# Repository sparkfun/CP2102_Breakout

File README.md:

CP2102 USB to Serial Breakout Board
===================================

[
*CP2102 USB to Serial Breakout (BOB-00198)*](https://www.sparkfun.com/products/198)

This breakout board enables you to connect to a standard USB A to B cable and communicate to your microcontroller via serial logic.

Repository Contents
-------------------
* **/Hardware** - All Eagle design files (.brd, .sch)
* **/Production** - Test bed files and production panel files

License Information
-------------------
The hardware is released under [Creative Commons ShareAlike 4.0 International](https://creativecommons.org/licenses/by-sa/4.0/).

Distributed as-is; no warranty is given.

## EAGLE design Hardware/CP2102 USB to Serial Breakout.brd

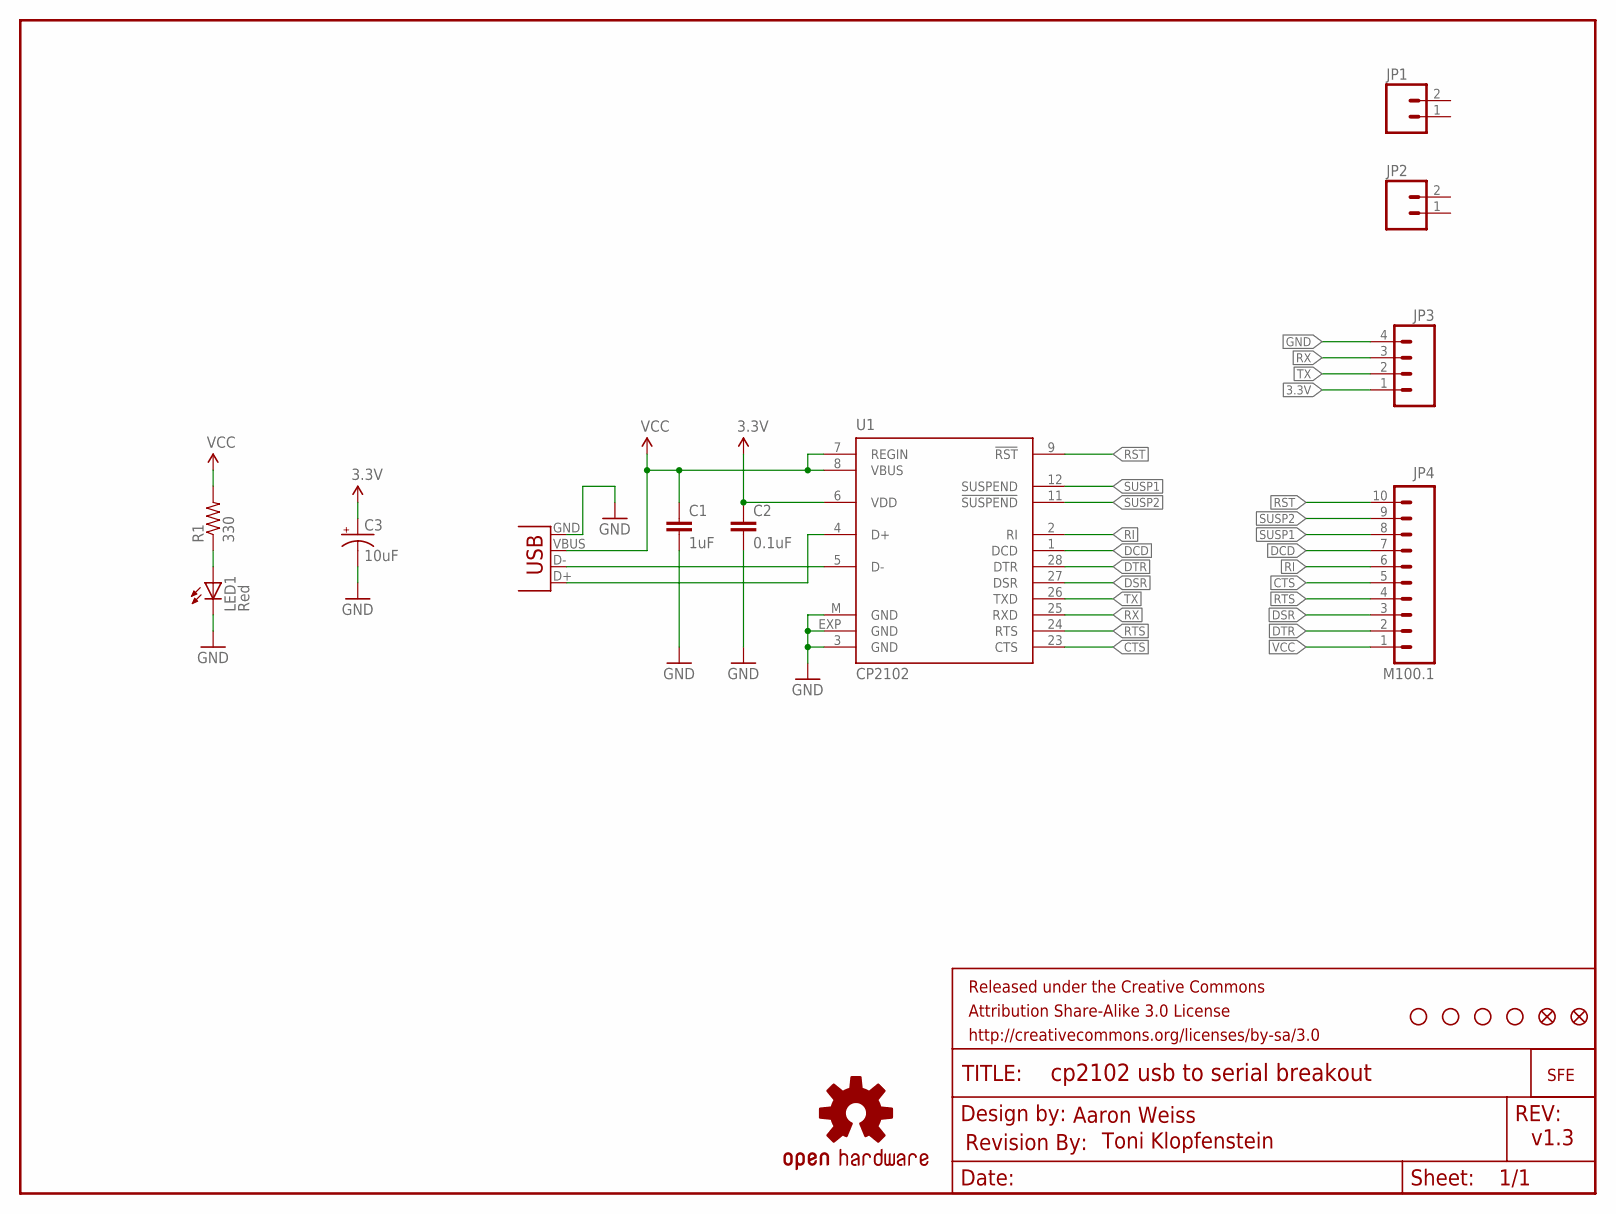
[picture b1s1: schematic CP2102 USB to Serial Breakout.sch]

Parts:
C1: 1uF; 0603-CAP
C2: 0.1uF; 0603-CAP
C3: 10uF; EIA3216
FID1, FID2: FIDUCIAL1X2; FIDUCIAL-1X2
FRAME1: FRAME-LETTER; CREATIVE_COMMONS
JP1, JP2: M02PTH; 1X02
JP3: M04PTH; 1X04
JP4: M100.1; 1X10
LED1: Red; LED-1206
LOGO1: OSHW-LOGOS; OSHW-LOGO-S
R1: 330; 0603-RES
U1: CP2102; MLP28
U$1: LOGO-SFENEW; SFE-NEW-WEBLOGO
U$4: REVISION
U$6, U$7, U$8, U$9: STAND-OFF
X1: USBPTH; USB-B-PTH

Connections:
3.3V: C2.1, C3.A (+), JP3.1, U1.6 (VDD)
CTS: JP4.5, U1.23 (CTS)
DCD: JP4.7, U1.1 (DCD)
DSR: JP4.3, U1.27 (DSR)
DTR: JP4.2, U1.28 (DTR)
GND: C1.2, C2.2, C3.C (-), JP3.4, LED1.C, U1.3 (GND), U1.EXP (GND), U1.M (GND), X1.GND
unnamed: U1.5 (D-), X1.D-
unnamed: U1.4 (D+), X1.D+
unnamed: LED1.A, R1.1
RI: JP4.6, U1.2 (RI)
RST: JP4.10, U1.9 (!RST)
RTS: JP4.4, U1.24 (RTS)
RX: JP3.3, U1.25 (RXD)
SUSP1: JP4.8, U1.12 (SUSPEND)
SUSP2: JP4.9, U1.11 (!SUSPEND)
TX: JP3.2, U1.26 (TXD)
VCC: C1.1, JP4.1, R1.2, U1.7 (REGIN), U1.8 (VBUS), X1.VBUS

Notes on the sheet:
Aaron Weiss
Toni Klopfenstein
v1.3

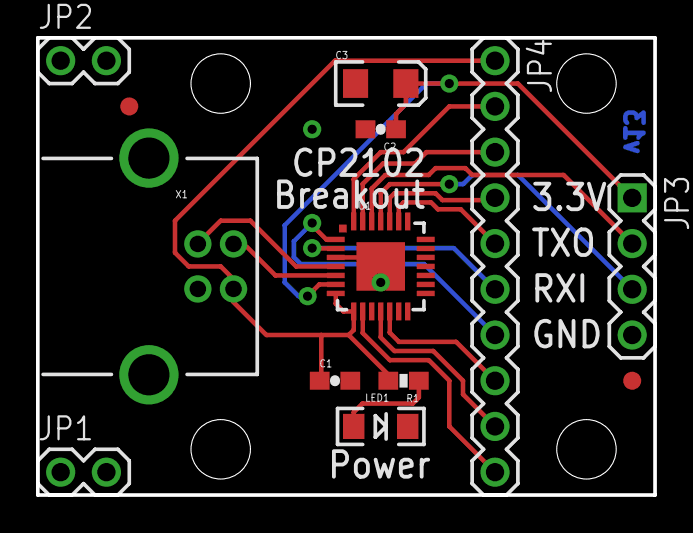
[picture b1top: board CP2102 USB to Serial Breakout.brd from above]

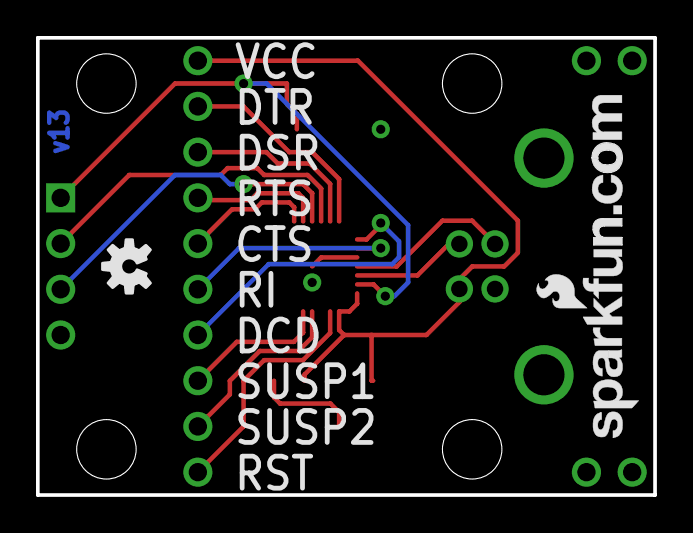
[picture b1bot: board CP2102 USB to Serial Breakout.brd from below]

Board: 2 copper layers, 34.3 x 25.4 mm, 21 parts (2 on the bottom side), 17 nets.

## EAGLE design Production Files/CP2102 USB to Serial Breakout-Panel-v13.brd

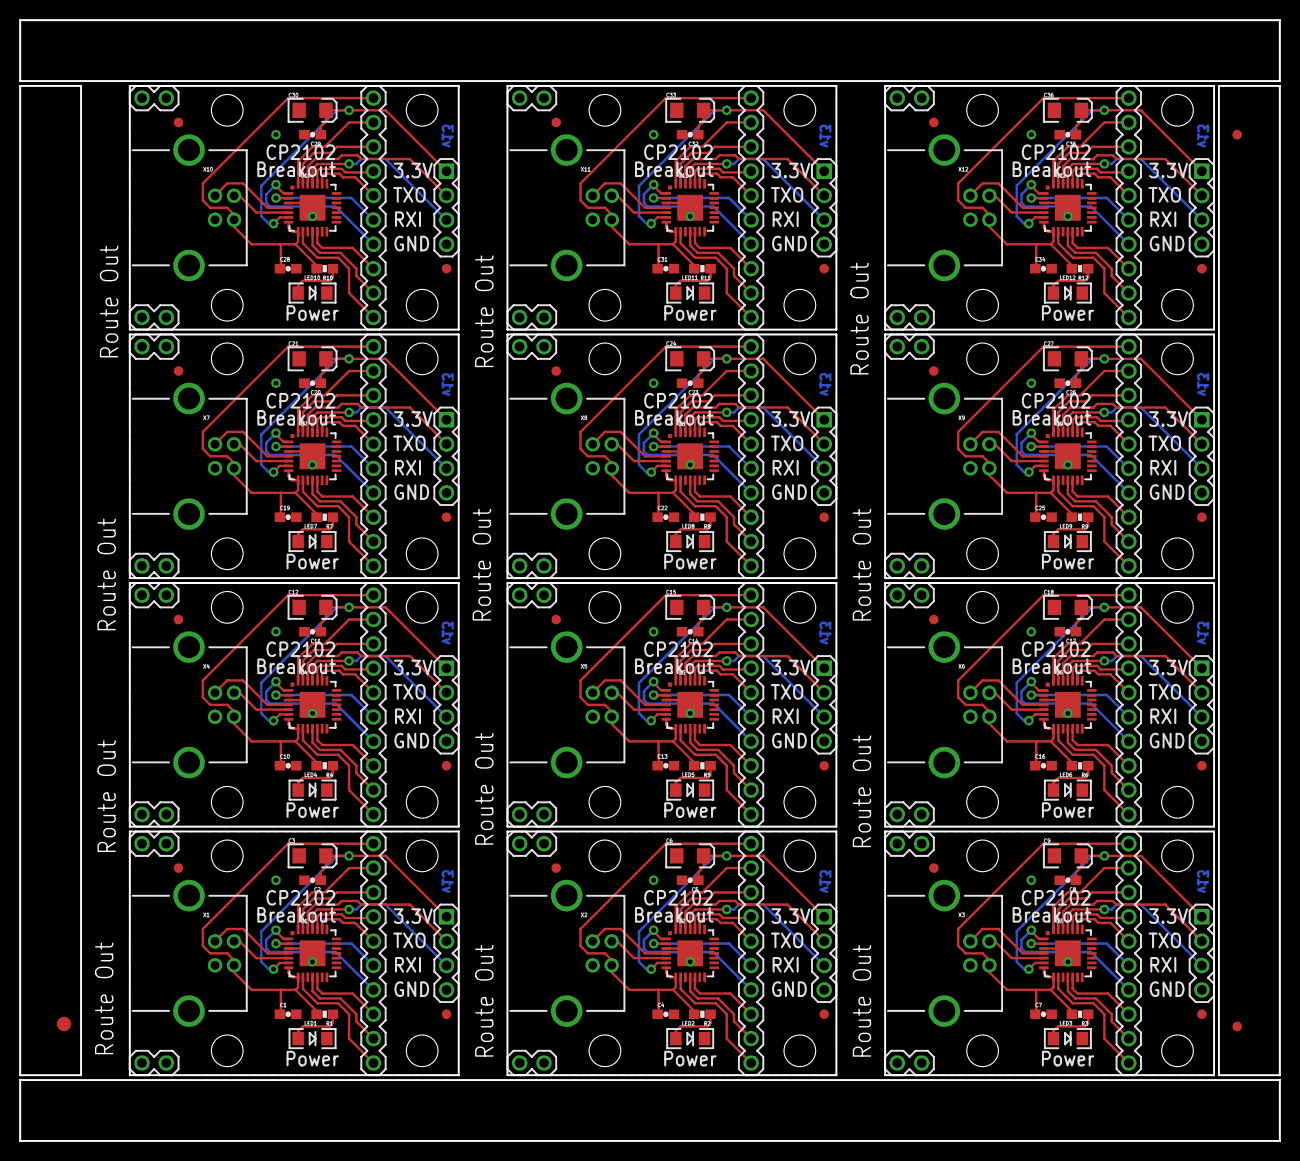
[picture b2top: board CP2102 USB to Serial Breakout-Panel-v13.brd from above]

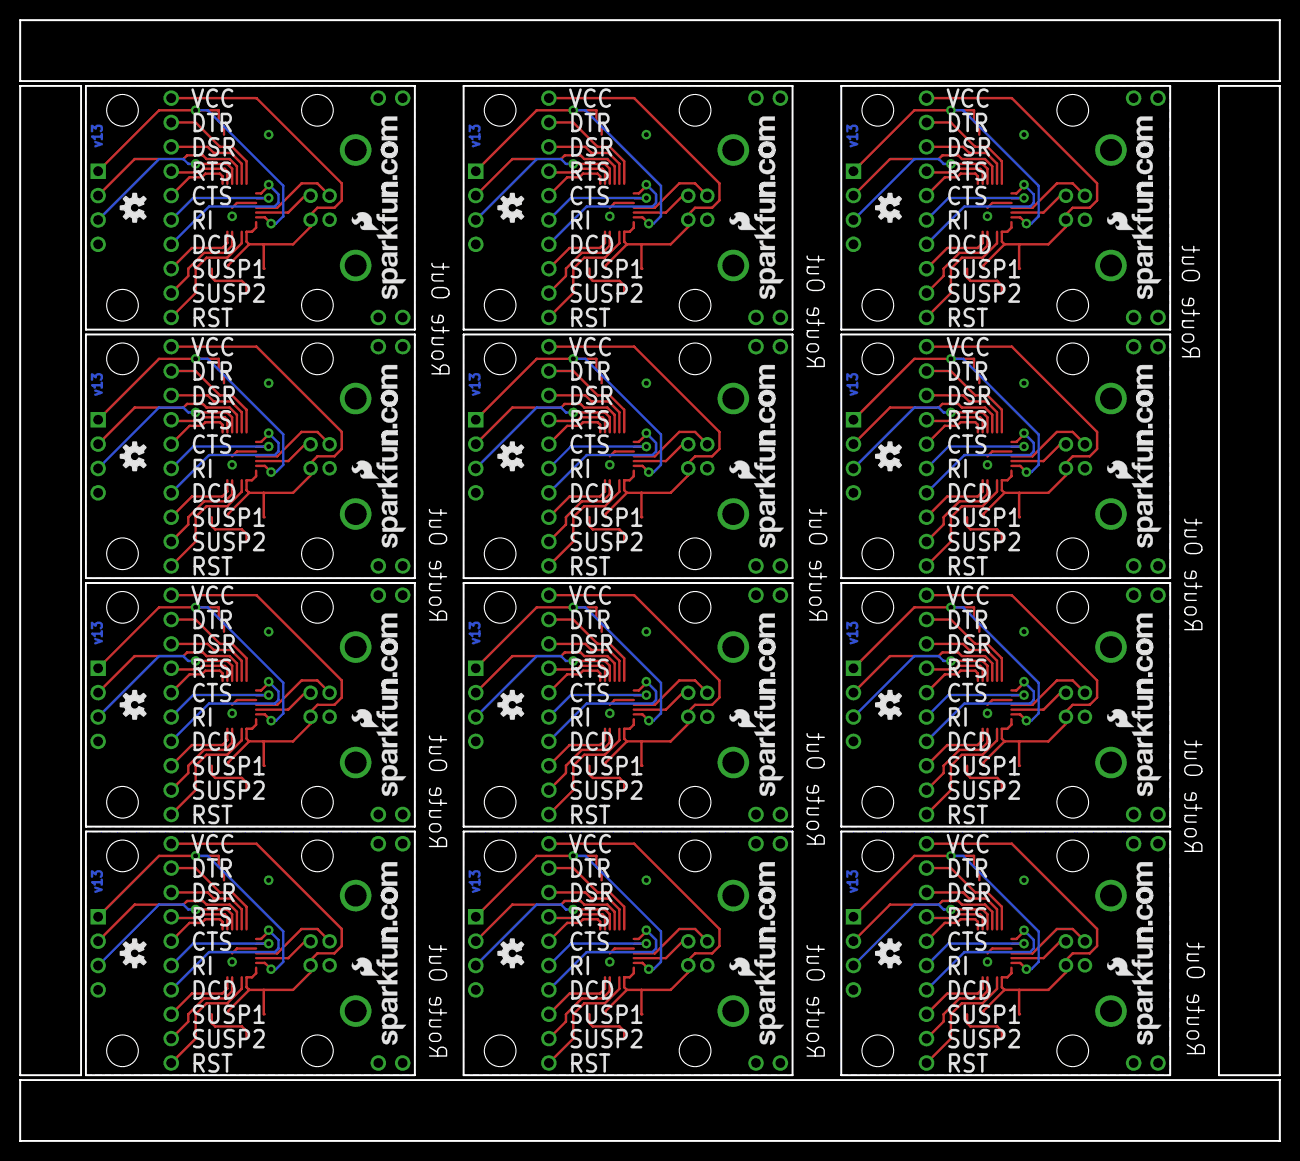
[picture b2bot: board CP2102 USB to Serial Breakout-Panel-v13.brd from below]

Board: 2 copper layers, 131.3 x 116.8 mm, 231 parts (24 on the bottom side), 204 nets.

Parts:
C1, C4, C7, C10, C13, C16, C19, C22, C25, C28, C31, C34: 1uF; 0603-CAP
C2, C5, C8, C11, C14, C17, C20, C23, C26, C29, C32, C35: 0.1uF; 0603-CAP
C3, C6, C9, C12, C15, C18, C21, C24, C27, C30, C33, C36: 10uF; EIA3216
E$1: FIDUCIAL-1.5X3
E$6, E$7: FIDUCIAL-1X2
FID1, FID2, FID3, FID4, FID5, FID6, FID7, FID8, FID9, FID10, FID11, FID12, FID13, FID14, FID15, FID16, FID17, FID18, FID19, FID20, FID21, FID22, FID23, FID24: FIDUCIAL1X2; FIDUCIAL-1X2
JP1, JP2, JP5, JP6, JP9, JP10, JP13, JP14, JP17, JP18, JP21, JP22, JP25, JP26, JP29, JP30, JP33, JP34, JP37, JP38, JP41, JP42, JP45, JP46: 1X02
JP3, JP7, JP11, JP15, JP19, JP23, JP27, JP31, JP35, JP39, JP43, JP47: 1X04
JP4, JP8, JP12, JP16, JP20, JP24, JP28, JP32, JP36, JP40, JP44, JP48: M100.1; 1X10
LED1, LED2, LED3, LED4, LED5, LED6, LED7, LED8, LED9, LED10, LED11, LED12: Red; LED-1206
LOGO1, LOGO2, LOGO3, LOGO4, LOGO5, LOGO6, LOGO7, LOGO8, LOGO9, LOGO10, LOGO11, LOGO12: OSHW-LOGOS; OSHW-LOGO-S
R1, R2, R3, R4, R5, R6, R7, R8, R9, R10, R11, R12: 330; 0603-RES
U1, U2, U3, U4, U5, U6, U7, U8, U9, U10, U11, U12: CP2102; MLP28
U$1, U$2, U$11, U$16, U$21, U$26, U$31, U$36, U$41, U$46, U$51, U$56: LOGO-SFENEW; SFE-NEW-WEBLOGO
U$3, U$4, U$5, U$6, U$7, U$8, U$9, U$10, U$12, U$13, U$14, U$15, U$17, U$18, U$19, U$20, U$22, U$23, U$24, U$25, U$27, U$28, U$29, U$30, U$32, U$33, U$34, U$35, U$37, U$38, U$39, U$40, U$42, U$43, U$44, U$45, U$47, U$48, U$49, U$50, U$52, U$53, U$54, U$55, U$57, U$58, U$59, U$60: STAND-OFF
X1, X2, X3, X4, X5, X6, X7, X8, X9, X10, X11, X12: USBPTH; USB-B-PTH

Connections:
3.3V: C2.1, C3.A, JP3.1, U1.6
3.3V1: C5.1, C6.A, JP7.1, U2.6
3.3V2: C8.1, C9.A, JP11.1, U3.6
3.3V3: C11.1, C12.A, JP15.1, U4.6
3.3V4: C14.1, C15.A, JP19.1, U5.6
3.3V5: C17.1, C18.A, JP23.1, U6.6
3.3V6: C20.1, C21.A, JP27.1, U7.6
3.3V7: C23.1, C24.A, JP31.1, U8.6
3.3V8: C26.1, C27.A, JP35.1, U9.6
3.3V9: C29.1, C30.A, JP39.1, U10.6
3.3V10: C32.1, C33.A, JP43.1, U11.6
3.3V11: C35.1, C36.A, JP47.1, U12.6
CTS: JP4.5, U1.23
CTS1: JP8.5, U2.23
CTS2: JP12.5, U3.23
CTS3: JP16.5, U4.23
CTS4: JP20.5, U5.23
CTS5: JP24.5, U6.23
CTS6: JP28.5, U7.23
CTS7: JP32.5, U8.23
CTS8: JP36.5, U9.23
CTS9: JP40.5, U10.23
CTS10: JP44.5, U11.23
CTS11: JP48.5, U12.23
DCD: JP4.7, U1.1
DCD1: JP8.7, U2.1
DCD2: JP12.7, U3.1
DCD3: JP16.7, U4.1
DCD4: JP20.7, U5.1
DCD5: JP24.7, U6.1
DCD6: JP28.7, U7.1
DCD7: JP32.7, U8.1
DCD8: JP36.7, U9.1
DCD9: JP40.7, U10.1
DCD10: JP44.7, U11.1
DCD11: JP48.7, U12.1
DSR: JP4.3, U1.27
DSR1: JP8.3, U2.27
DSR2: JP12.3, U3.27
DSR3: JP16.3, U4.27
DSR4: JP20.3, U5.27
DSR5: JP24.3, U6.27
DSR6: JP28.3, U7.27
DSR7: JP32.3, U8.27
DSR8: JP36.3, U9.27
DSR9: JP40.3, U10.27
DSR10: JP44.3, U11.27
DSR11: JP48.3, U12.27
DTR: JP4.2, U1.28
DTR1: JP8.2, U2.28
DTR2: JP12.2, U3.28
DTR3: JP16.2, U4.28
DTR4: JP20.2, U5.28
DTR5: JP24.2, U6.28
DTR6: JP28.2, U7.28
DTR7: JP32.2, U8.28
DTR8: JP36.2, U9.28
DTR9: JP40.2, U10.28
DTR10: JP44.2, U11.28
DTR11: JP48.2, U12.28
GND: C1.2, C2.2, C3.C, JP3.4, LED1.C, U1.3, U1.EXP, U1.M, X1.GND
GND1: C4.2, C5.2, C6.C, JP7.4, LED2.C, U2.3, U2.EXP, U2.M, X2.GND
GND2: C7.2, C8.2, C9.C, JP11.4, LED3.C, U3.3, U3.EXP, U3.M, X3.GND
GND3: C10.2, C11.2, C12.C, JP15.4, LED4.C, U4.3, U4.EXP, U4.M, X4.GND
GND4: C13.2, C14.2, C15.C, JP19.4, LED5.C, U5.3, U5.EXP, U5.M, X5.GND
GND5: C16.2, C17.2, C18.C, JP23.4, LED6.C, U6.3, U6.EXP, U6.M, X6.GND
GND6: C19.2, C20.2, C21.C, JP27.4, LED7.C, U7.3, U7.EXP, U7.M, X7.GND
GND7: C22.2, C23.2, C24.C, JP31.4, LED8.C, U8.3, U8.EXP, U8.M, X8.GND
GND8: C25.2, C26.2, C27.C, JP35.4, LED9.C, U9.3, U9.EXP, U9.M, X9.GND
GND9: C28.2, C29.2, C30.C, JP39.4, LED10.C, U10.3, U10.EXP, U10.M, X10.GND
GND10: C31.2, C32.2, C33.C, JP43.4, LED11.C, U11.3, U11.EXP, U11.M, X11.GND
GND11: C34.2, C35.2, C36.C, JP47.4, LED12.C, U12.3, U12.EXP, U12.M, X12.GND
unnamed: U1.5, X1.D-
unnamed: U1.4, X1.D+
unnamed: LED1.A, R1.1
unnamed: U2.5, X2.D-
unnamed: U2.4, X2.D+
unnamed: LED2.A, R2.1
unnamed: U3.5, X3.D-
unnamed: U3.4, X3.D+
unnamed: LED3.A, R3.1
unnamed: U4.5, X4.D-
unnamed: U4.4, X4.D+
unnamed: LED4.A, R4.1
unnamed: U5.5, X5.D-
unnamed: U5.4, X5.D+
unnamed: LED5.A, R5.1
unnamed: U6.5, X6.D-
unnamed: U6.4, X6.D+
unnamed: LED6.A, R6.1
unnamed: U7.5, X7.D-
unnamed: U7.4, X7.D+
unnamed: LED7.A, R7.1
unnamed: U8.5, X8.D-
unnamed: U8.4, X8.D+
unnamed: LED8.A, R8.1
unnamed: U9.5, X9.D-
unnamed: U9.4, X9.D+
unnamed: LED9.A, R9.1
unnamed: U10.5, X10.D-
unnamed: U10.4, X10.D+
unnamed: LED10.A, R10.1
unnamed: U11.5, X11.D-
unnamed: U11.4, X11.D+
unnamed: LED11.A, R11.1
unnamed: U12.5, X12.D-
unnamed: U12.4, X12.D+
unnamed: LED12.A, R12.1
RI: JP4.6, U1.2
RI1: JP8.6, U2.2
RI2: JP12.6, U3.2
RI3: JP16.6, U4.2
RI4: JP20.6, U5.2
RI5: JP24.6, U6.2
RI6: JP28.6, U7.2
RI7: JP32.6, U8.2
RI8: JP36.6, U9.2
RI9: JP40.6, U10.2
RI10: JP44.6, U11.2
RI11: JP48.6, U12.2
RST: JP4.10, U1.9
RST1: JP8.10, U2.9
RST2: JP12.10, U3.9
RST3: JP16.10, U4.9
RST4: JP20.10, U5.9
RST5: JP24.10, U6.9
RST6: JP28.10, U7.9
RST7: JP32.10, U8.9
RST8: JP36.10, U9.9
RST9: JP40.10, U10.9
RST10: JP44.10, U11.9
RST11: JP48.10, U12.9
RTS: JP4.4, U1.24
RTS1: JP8.4, U2.24
RTS2: JP12.4, U3.24
RTS3: JP16.4, U4.24
RTS4: JP20.4, U5.24
RTS5: JP24.4, U6.24
RTS6: JP28.4, U7.24
RTS7: JP32.4, U8.24
RTS8: JP36.4, U9.24
RTS9: JP40.4, U10.24
RTS10: JP44.4, U11.24
RTS11: JP48.4, U12.24
RX: JP3.3, U1.25
RX1: JP7.3, U2.25
RX2: JP11.3, U3.25
RX3: JP15.3, U4.25
RX4: JP19.3, U5.25
RX5: JP23.3, U6.25
RX6: JP27.3, U7.25
RX7: JP31.3, U8.25
RX8: JP35.3, U9.25
RX9: JP39.3, U10.25
RX10: JP43.3, U11.25
RX11: JP47.3, U12.25
SUSP1: JP4.8, U1.12
SUSP2: JP4.9, U1.11
SUSP3: JP8.8, U2.12
SUSP4: JP8.9, U2.11
SUSP5: JP12.8, U3.12
SUSP6: JP12.9, U3.11
SUSP7: JP16.8, U4.12
SUSP8: JP16.9, U4.11
SUSP9: JP20.8, U5.12
SUSP10: JP20.9, U5.11
SUSP11: JP24.8, U6.12
SUSP12: JP24.9, U6.11
SUSP13: JP28.8, U7.12
SUSP14: JP28.9, U7.11
SUSP15: JP32.8, U8.12
SUSP16: JP32.9, U8.11
SUSP17: JP36.8, U9.12
SUSP18: JP36.9, U9.11
SUSP19: JP40.8, U10.12
SUSP20: JP40.9, U10.11
SUSP21: JP44.8, U11.12
SUSP22: JP44.9, U11.11
SUSP23: JP48.8, U12.12
SUSP24: JP48.9, U12.11
TX: JP3.2, U1.26
TX1: JP7.2, U2.26
TX2: JP11.2, U3.26
TX3: JP15.2, U4.26
TX4: JP19.2, U5.26
TX5: JP23.2, U6.26
TX6: JP27.2, U7.26
TX7: JP31.2, U8.26
TX8: JP35.2, U9.26
TX9: JP39.2, U10.26
TX10: JP43.2, U11.26
TX11: JP47.2, U12.26
VCC: C1.1, JP4.1, R1.2, U1.7, U1.8, X1.VBUS
VCC1: C4.1, JP8.1, R2.2, U2.7, U2.8, X2.VBUS
VCC2: C7.1, JP12.1, R3.2, U3.7, U3.8, X3.VBUS
VCC3: C10.1, JP16.1, R4.2, U4.7, U4.8, X4.VBUS
VCC4: C13.1, JP20.1, R5.2, U5.7, U5.8, X5.VBUS
VCC5: C16.1, JP24.1, R6.2, U6.7, U6.8, X6.VBUS
VCC6: C19.1, JP28.1, R7.2, U7.7, U7.8, X7.VBUS
VCC7: C22.1, JP32.1, R8.2, U8.7, U8.8, X8.VBUS
VCC8: C25.1, JP36.1, R9.2, U9.7, U9.8, X9.VBUS
VCC9: C28.1, JP40.1, R10.2, U10.7, U10.8, X10.VBUS
VCC10: C31.1, JP44.1, R11.2, U11.7, U11.8, X11.VBUS
VCC11: C34.1, JP48.1, R12.2, U12.7, U12.8, X12.VBUS

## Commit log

2014-02-07 Initial file commit
2014-02-07 Version 1.3 files
2014-02-10 Updating board file name
2014-02-11 changed micro fiducial to regular
2014-02-11 created panel v13
2014-02-12 Update README.md
    Fixing part number from CP2101 to CP2102.
2014-08-12 Updating README with Production file description
2025-06-27 Update README.md
    Updating link

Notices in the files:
parts and their libraries:
SparkFun-Resistors: Licensing: CC v3.0 Share-Alike You are welcome to use this library for commercial purposes.
SparkFun-Aesthetics: Released under the Creative Commons Attribution Share-Alike 3.0 License
SparkFun-Aesthetics: http://creativecommons.org/licenses/by-sa/3.0
